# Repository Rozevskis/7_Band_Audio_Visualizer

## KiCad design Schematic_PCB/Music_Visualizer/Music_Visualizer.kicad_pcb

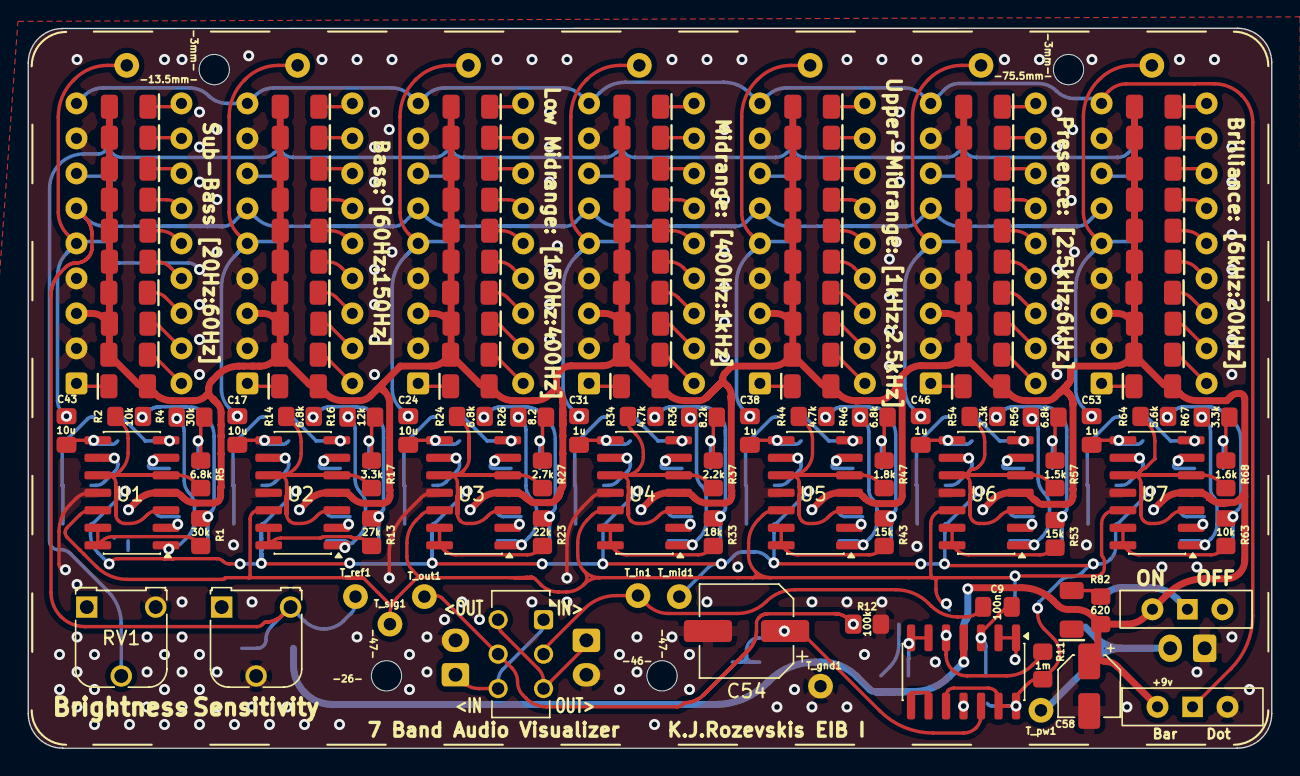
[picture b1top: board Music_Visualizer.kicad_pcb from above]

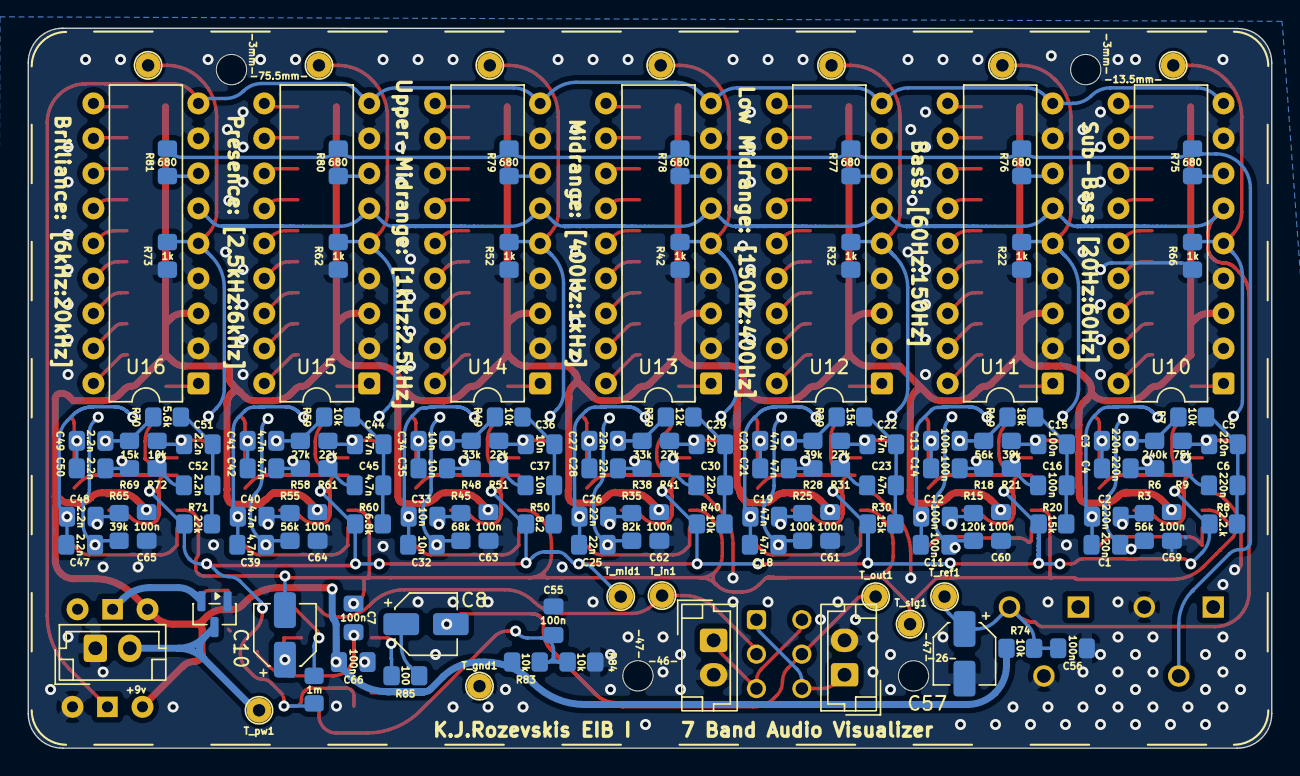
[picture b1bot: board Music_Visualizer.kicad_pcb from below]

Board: 2 copper layers, 90.2 x 52.2 mm, 264 parts (135 on the bottom side), 175 nets.

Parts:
C1, C2, C3, C4, C5, C6: 220n; custom_C_0805_2012Metric_Pad1.18x1.45mm_HandSolder
C7, C9, C11, C12, C13, C14, C15, C16, C55, C56, C59, C60, C61, C62, C63, C64, C65, C66: 100n; custom_C_0805_2012Metric_Pad1.18x1.45mm_HandSolder
C8, C10, C57, C58: 10u; CP_Elec_4x5.4
C17, C24, C43: 10u; custom_C_0805_2012Metric_Pad1.18x1.45mm_HandSolder
C18, C19, C20, C21, C22, C23: 47n; custom_C_0805_2012Metric_Pad1.18x1.45mm_HandSolder
C25, C26, C27, C28, C29, C30: 22n; custom_C_0805_2012Metric_Pad1.18x1.45mm_HandSolder
C31, C38, C46, C53: 1u; custom_C_0805_2012Metric_Pad1.18x1.45mm_HandSolder
C32, C33, C34, C35, C36, C37: 10n; custom_C_0805_2012Metric_Pad1.18x1.45mm_HandSolder
C39, C40, C41, C42, C44, C45: 4.7n; custom_C_0805_2012Metric_Pad1.18x1.45mm_HandSolder
C47, C48, C49, C50, C51, C52: 2.2n; custom_C_0805_2012Metric_Pad1.18x1.45mm_HandSolder
C54: 47u; CP_Elec_6.3x5.3
D1, D2, D3, D4, D5, D6, D7, D11, D12, D13, D14, D15, D16, D17, D21, D22, D23, D24, D25, D26, D27, D31, D32, D33, D34, D35, D36, D37, D41, D42, D43, D44, D45, D46, D47, D51, D52, D53, D54, D55, D56, D57, D61, D62, D63, D64, D65, D66, D67: LED; LED_1206_3216Metric_Green
D8, D9, D18, D19, D28, D29, D38, D39, D48, D49, D58, D59, D68, D69: LED; LED_1206_3216Metric_Yellow
D10, D20, D30, D40, D50, D60, D70, D71: LED; LED_1206_3216Metric_Red
H1, H2, H3, H4: MountingHole; Apgriezts_MountingHole_2.2mm_M2
J3, J5: Screw_Terminal_01x02; JST_EH_B2B-EH-A_1x02_P2.50mm_Vertical
J6: 3.5mm; JST_EH_B2B-EH-A_1x02_P2.50mm_Vertical
Q1: DMP2123LQ-7; SOT-23
R1, R4: 30k; R_0805_2012Metric_Pad1.20x1.40mm_HandSolder
R2, R7, R40, R49, R59, R63, R72, R74, R83, R84: 10k; R_0805_2012Metric_Pad1.20x1.40mm_HandSolder
R3, R18, R55: 56k; R_0805_2012Metric_Pad1.20x1.40mm_HandSolder
R5, R14, R24, R46, R56, R60: 6.8k; R_0805_2012Metric_Pad1.20x1.40mm_HandSolder
R6: 240k; R_0805_2012Metric_Pad1.20x1.40mm_HandSolder
R8: 2.2.k; R_0805_2012Metric_Pad1.20x1.40mm_HandSolder
R9: 75k; R_0805_2012Metric_Pad1.20x1.40mm_HandSolder
R10, R11: 1m; R_0805_2012Metric_Pad1.20x1.40mm_HandSolder
R12, R25: 100k; R_0805_2012Metric_Pad1.20x1.40mm_HandSolder
R13, R31, R41, R58: 27k; R_0805_2012Metric_Pad1.20x1.40mm_HandSolder
R15: 120k; R_0805_2012Metric_Pad1.20x1.40mm_HandSolder
R16, R39: 12k; R_0805_2012Metric_Pad1.20x1.40mm_HandSolder
R17, R54, R67: 3.3k; R_0805_2012Metric_Pad1.20x1.40mm_HandSolder
R19, R33: 18k; R_0805_2012Metric_Pad1.20x1.40mm_HandSolder
R20, R29, R30, R43, R53, R69: 15k; R_0805_2012Metric_Pad1.20x1.40mm_HandSolder
R21, R28, R65: 39k; R_0805_2012Metric_Pad1.20x1.40mm_HandSolder
R22, R32, R42, R52, R62, R66, R73: 1k; R_0805_2012Metric_Pad1.20x1.40mm_HandSolder
R23, R51, R61, R71: 22k; R_0805_2012Metric_Pad1.20x1.40mm_HandSolder
R26, R50: 8.2; R_0805_2012Metric_Pad1.20x1.40mm_HandSolder
R27: 2.7k; R_0805_2012Metric_Pad1.20x1.40mm_HandSolder
R34, R44: 4.7k; R_0805_2012Metric_Pad1.20x1.40mm_HandSolder
R35: 82k; R_0805_2012Metric_Pad1.20x1.40mm_HandSolder
R36: 8.2k; R_0805_2012Metric_Pad1.20x1.40mm_HandSolder
R37: 2.2k; R_0805_2012Metric_Pad1.20x1.40mm_HandSolder
R38, R48: 33k; R_0805_2012Metric_Pad1.20x1.40mm_HandSolder
R45: 68k; R_0805_2012Metric_Pad1.20x1.40mm_HandSolder
R47: 1.8k; R_0805_2012Metric_Pad1.20x1.40mm_HandSolder
R57: 1.5k; R_0805_2012Metric_Pad1.20x1.40mm_HandSolder
R64, R70: 5.6k; R_0805_2012Metric_Pad1.20x1.40mm_HandSolder
R68: 1.6k; R_0805_2012Metric_Pad1.20x1.40mm_HandSolder
R75, R76, R77, R78, R79, R80, R81: 680; R_0805_2012Metric_Pad1.20x1.40mm_HandSolder
R82: 620; R_0805_2012Metric_Pad1.20x1.40mm_HandSolder
R85: 100; R_0805_2012Metric_Pad1.20x1.40mm_HandSolder
RV1: 1k_LED_Brightness_Pot; Potentiometer_Runtron_RM-065_Vertical
RV2: 1k_Rhi_Adjuster; Potentiometer_Runtron_RM-065_Vertical
SW1: SW_Slide_DPDT; SW_CK_JS202011CQN_DPDT_Straight
SW2, SW3: SW_SPST; SW_Slide-03_Wuerth-WS-SLTV_10x2.5x6.4_P2.54mm
TP1: T_SB; NEW_2_TestPoint_Loop_D2.60mm_Drill0.9mm_Beaded
TP2: T_B; NEW_2_TestPoint_Loop_D2.60mm_Drill0.9mm_Beaded
TP3: T_LM; NEW_2_TestPoint_Loop_D2.60mm_Drill0.9mm_Beaded
TP4: T_M; NEW_2_TestPoint_Loop_D2.60mm_Drill0.9mm_Beaded
TP5: T_UM; NEW_2_TestPoint_Loop_D2.60mm_Drill0.9mm_Beaded
TP6: V_MH; NEW_2_TestPoint_Loop_D2.60mm_Drill0.9mm_Beaded
TP7: V_H; NEW_2_TestPoint_Loop_D2.60mm_Drill0.9mm_Beaded
T_gnd1: T_gnd; NEW_2_TestPoint_Loop_D2.60mm_Drill0.9mm_Beaded
T_in1: T_in; NEW_2_TestPoint_Loop_D2.60mm_Drill0.9mm_Beaded
T_mid1: T_mid; NEW_2_TestPoint_Loop_D2.60mm_Drill0.9mm_Beaded
T_out1: T_out; NEW_2_TestPoint_Loop_D2.60mm_Drill0.9mm_Beaded
T_pw1: T_pw; NEW_2_TestPoint_Loop_D2.60mm_Drill0.9mm_Beaded
T_ref1: T_ref; NEW_2_TestPoint_Loop_D2.60mm_Drill0.9mm_Beaded
T_sig1: T_sig; NEW_2_TestPoint_Loop_D2.60mm_Drill0.9mm_Beaded
U1, U2, U3, U4, U5, U6, U7, U8: LM324; SOIC-14_3.9x8.7mm_P1.27mm
U10, U11, U12, U13, U14, U15, U16: LM3915N-1; DIP-18_W7.62mm

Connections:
+9V: C58.1, C59.2, C60.2, C61.2, C62.2, C63.2, C64.2, C65.2, C66.2, D1.2 (A), D2.2 (A), D3.2 (A), D4.2 (A), D5.2 (A), D6.2 (A), D7.2 (A), D8.2 (A), D9.2 (A), D10.2 (A), D11.2 (A), D12.2 (A), D13.2 (A), D14.2 (A), D15.2 (A), D16.2 (A), D17.2 (A), D18.2 (A), D19.2 (A), D20.2 (A), D21.2 (A), D22.2 (A), D23.2 (A), D24.2 (A), D25.2 (A), D26.2 (A), D27.2 (A), D28.2 (A), D29.2 (A), D30.2 (A), D31.2 (A), D32.2 (A), D33.2 (A), D34.2 (A), D35.2 (A), D36.2 (A), D37.2 (A), D38.2 (A), D39.2 (A), D40.2 (A), D41.2 (A), D42.2 (A), D43.2 (A), D44.2 (A), D45.2 (A), D46.2 (A), D47.2 (A), D48.2 (A), D49.2 (A), D50.2 (A), D51.2 (A), D52.2 (A), D53.2 (A), D54.2 (A), D55.2 (A), D56.2 (A), D57.2 (A), D58.2 (A), D59.2 (A), D60.2 (A), D61.2 (A), D62.2 (A), D63.2 (A), D64.2 (A), D65.2 (A), D66.2 (A), D67.2 (A), D68.2 (A), D69.2 (A), D70.2 (A), R74.1, R82.1, R83.2, SW2.2 (B), SW3.1 (C), U1.4 (V+), U2.4 (V+), U3.4 (V+), U4.4 (V+), U5.4 (V+), U6.4 (V+), U7.4 (V+), U8.4 (V+), U10.3 (V+), U11.3 (V+), U12.3 (V+), U13.3 (V+), U14.3 (V+), U15.3 (V+), U16.3 (V+)
GND: C54.2, C55.1, C56.1, C57.2, C58.2, C59.1, C60.1, C61.1, C62.1, C63.1, C64.1, C65.1, C66.1, D71.1 (K), J3.2, J5.2, J6.1 (-), Q1.2 (G), R12.2, R22.2, R32.2, R42.2, R52.2, R62.2, R66.2, R73.2, R84.1, RV1.3, RV2.2, SW3.3 (A), T_gnd1.1 (1_1), U1.11 (V-), U2.11 (V-), U3.11 (V-), U4.11 (V-), U5.11 (V-), U6.11 (V-), U7.11 (V-), U8.11 (V-), U10.2 (V-), U10.4 (RLO), U10.8 (REF_ADJ), U11.2 (V-), U11.4 (RLO), U11.8 (REF_ADJ), U12.2 (V-), U12.4 (RLO), U12.8 (REF_ADJ), U13.2 (V-), U13.4 (RLO), U13.8 (REF_ADJ), U14.2 (V-), U14.4 (RLO), U14.8 (REF_ADJ), U15.2 (V-), U15.4 (RLO), U15.8 (REF_ADJ), U16.2 (V-), U16.4 (RLO), U16.8 (REF_ADJ)
LED_Brightness_Control: R75.2, R76.2, R77.2, R78.2, R79.2, R80.2, R81.2, RV1.2
Left jack: J3.1, SW1.1 (A), SW1.4 (A)
Mode: SW3.2 (B), U10.9 (MODE), U11.9 (MODE), U12.9 (MODE), U13.9 (MODE), U14.9 (MODE), U15.9 (MODE), U16.9 (MODE)
unnamed: C1.1, C2.1, R1.2, R2.1
unnamed: C1.2, R3.1, R4.1, U1.1
unnamed: C3.1, C4.1, R4.2, R5.1
unnamed: C3.2, R6.1, R7.1, U1.7
unnamed: C5.1, C6.1, R7.2, R8.1
unnamed: C8.1, R85.2
unnamed: C8.2, R12.1, SW1.5 (B), T_out1.1 (1_1)
unnamed: C9.1, SW1.2 (B), T_in1.1 (1_1)
unnamed: C11.1, C12.1, R13.2, R14.1
unnamed: C11.2, R15.1, R16.1, U2.1
unnamed: C13.1, C14.1, R16.2, R17.1
unnamed: C13.2, R18.1, R19.1, U2.7
unnamed: C15.1, C16.1, R19.2, R20.1
unnamed: C15.2, C17.1, R21.1, U2.8
unnamed: C18.1, C19.1, R23.2, R24.1
unnamed: C18.2, R25.1, R26.1, U3.1
unnamed: C20.1, C21.1, R26.2, R27.1
unnamed: C20.2, R28.1, R29.1, U3.7
unnamed: C22.1, C23.1, R29.2, R30.1
unnamed: C22.2, C24.1, R31.1, U3.8
unnamed: C25.1, C26.1, R33.2, R34.1
unnamed: C25.2, R35.1, R36.1, U4.1
unnamed: C27.1, C28.1, R36.2, R37.1
unnamed: C27.2, R38.1, R39.1, U4.7
unnamed: C29.1, C30.1, R39.2, R40.1
unnamed: C29.2, C31.1, R41.1, U4.8
unnamed: C32.1, C33.1, R43.2, R44.1
unnamed: C32.2, R45.1, R46.1, U5.1
unnamed: C34.1, C35.1, R46.2, R47.1
unnamed: C34.2, R48.1, R49.1, U5.7
unnamed: C36.1, C37.1, R49.2, R50.1
unnamed: C36.2, C38.1, R51.1, U5.8
unnamed: C39.1, C40.1, R53.2, R54.1
unnamed: C39.2, R55.1, R56.1, U6.1
unnamed: C41.1, C42.1, R56.2, R57.1
unnamed: C41.2, R58.1, R59.1, U6.7
unnamed: C5.2, C43.2, R9.1, U1.8
unnamed: C44.1, C45.1, R59.2, R60.1
unnamed: C44.2, C46.1, R61.1, U6.8
unnamed: C47.1, C48.1, R63.2, R64.1
unnamed: C47.2, R65.1, R67.1, U7.1
unnamed: C49.1, C50.1, R67.2, R68.1
unnamed: C49.2, R69.1, R70.1, U7.7
unnamed: C51.1, C52.1, R70.2, R71.1
unnamed: C51.2, C53.1, R72.1, U7.8
unnamed: D1.1 (K), U10.1 (LED1_K)
unnamed: D2.1 (K), U10.18 (LED2_K)
unnamed: D3.1 (K), U10.17 (LED3_K)
unnamed: D4.1 (K), U10.16 (LED4_K)
unnamed: D5.1 (K), U10.15 (LED5_K)
unnamed: D6.1 (K), U10.14 (LED6_K)
unnamed: D7.1 (K), U10.13 (LED7_K)
unnamed: D8.1 (K), U10.12 (LED8_K)
unnamed: D9.1 (K), U10.11 (LED9_K)
unnamed: D10.1 (K), U10.10 (LED10_K)
unnamed: D11.1 (K), U11.1 (LED1_K)
unnamed: D12.1 (K), U11.18 (LED2_K)
unnamed: D13.1 (K), U11.17 (LED3_K)
unnamed: D14.1 (K), U11.16 (LED4_K)
unnamed: D15.1 (K), U11.15 (LED5_K)
unnamed: D16.1 (K), U11.14 (LED6_K)
unnamed: D17.1 (K), U11.13 (LED7_K)
unnamed: D18.1 (K), U11.12 (LED8_K)
unnamed: D19.1 (K), U11.11 (LED9_K)
unnamed: D20.1 (K), U11.10 (LED10_K)
unnamed: D21.1 (K), U12.1 (LED1_K)
unnamed: D22.1 (K), U12.18 (LED2_K)
unnamed: D23.1 (K), U12.17 (LED3_K)
unnamed: D24.1 (K), U12.16 (LED4_K)
unnamed: D25.1 (K), U12.15 (LED5_K)
unnamed: D26.1 (K), U12.14 (LED6_K)
unnamed: D27.1 (K), U12.13 (LED7_K)
unnamed: D28.1 (K), U12.12 (LED8_K)
unnamed: D29.1 (K), U12.11 (LED9_K)
unnamed: D30.1 (K), U12.10 (LED10_K)
unnamed: D31.1 (K), U13.1 (LED1_K)
unnamed: D32.1 (K), U13.18 (LED2_K)
unnamed: D33.1 (K), U13.17 (LED3_K)
unnamed: D34.1 (K), U13.16 (LED4_K)
unnamed: D35.1 (K), U13.15 (LED5_K)
unnamed: D36.1 (K), U13.14 (LED6_K)
unnamed: D37.1 (K), U13.13 (LED7_K)
unnamed: D38.1 (K), U13.12 (LED8_K)
unnamed: D39.1 (K), U13.11 (LED9_K)
unnamed: D40.1 (K), U13.10 (LED10_K)
unnamed: D41.1 (K), U14.1 (LED1_K)
unnamed: D42.1 (K), U14.18 (LED2_K)
unnamed: D43.1 (K), U14.17 (LED3_K)
unnamed: D44.1 (K), U14.16 (LED4_K)
unnamed: D45.1 (K), U14.15 (LED5_K)
unnamed: D46.1 (K), U14.14 (LED6_K)
unnamed: D47.1 (K), U14.13 (LED7_K)
unnamed: D48.1 (K), U14.12 (LED8_K)
unnamed: D49.1 (K), U14.11 (LED9_K)
unnamed: D50.1 (K), U14.10 (LED10_K)
unnamed: D51.1 (K), U15.1 (LED1_K)
unnamed: D52.1 (K), U15.18 (LED2_K)
unnamed: D53.1 (K), U15.17 (LED3_K)
unnamed: D54.1 (K), U15.16 (LED4_K)
unnamed: D55.1 (K), U15.15 (LED5_K)
unnamed: D56.1 (K), U15.14 (LED6_K)
unnamed: D57.1 (K), U15.13 (LED7_K)
unnamed: D58.1 (K), U15.12 (LED8_K)
unnamed: D59.1 (K), U15.11 (LED9_K)
unnamed: D60.1 (K), U15.10 (LED10_K)
unnamed: D61.1 (K), U16.1 (LED1_K)
unnamed: D62.1 (K), U16.18 (LED2_K)
unnamed: D63.1 (K), U16.17 (LED3_K)
unnamed: D64.1 (K), U16.16 (LED4_K)
unnamed: D65.1 (K), U16.15 (LED5_K)
unnamed: D66.1 (K), U16.14 (LED6_K)
unnamed: D67.1 (K), U16.13 (LED7_K)
unnamed: D68.1 (K), U16.12 (LED8_K)
unnamed: D69.1 (K), U16.11 (LED9_K)
unnamed: D70.1 (K), U16.10 (LED10_K)
unnamed: D71.2 (A), R82.2
unnamed: J6.2 (+), Q1.1 (D), T_pw1.1 (1_1)
unnamed: Q1.3 (S), SW2.1 (A)
unnamed: C2.2, R3.2, U1.2 (-)
unnamed: C4.2, R6.2, U1.6 (-)
unnamed: C6.2, R9.2, U1.9 (-)
unnamed: R1.1, U1.13 (-), U1.14
unnamed: C12.2, R15.2, U2.2 (-)
unnamed: C14.2, R18.2, U2.6 (-)
unnamed: C16.2, R21.2, U2.9 (-)
unnamed: R13.1, U2.13 (-), U2.14
unnamed: C19.2, R25.2, U3.2 (-)
unnamed: C21.2, R28.2, U3.6 (-)
unnamed: C23.2, R31.2, U3.9 (-)
unnamed: R23.1, U3.13 (-), U3.14
unnamed: C26.2, R35.2, U4.2 (-)
unnamed: C28.2, R38.2, U4.6 (-)
unnamed: C30.2, R41.2, U4.9 (-)
unnamed: R33.1, U4.13 (-), U4.14
unnamed: C33.2, R45.2, U5.2 (-)
unnamed: C35.2, R48.2, U5.6 (-)
unnamed: C37.2, R51.2, U5.9 (-)
unnamed: R43.1, U5.13 (-), U5.14
unnamed: C40.2, R55.2, U6.2 (-)
unnamed: C42.2, R58.2, U6.6 (-)
unnamed: C45.2, R61.2, U6.9 (-)
unnamed: R53.1, U6.13 (-), U6.14
unnamed: C48.2, R65.2, U7.2 (-)
unnamed: C50.2, R69.2, U7.6 (-)
unnamed: C52.2, R72.2, U7.9 (-)
unnamed: R63.1, U7.13 (-), U7.14
unnamed: C9.2, R10.1, U8.3 (+)
unnamed: C10.1, U8.1, U8.2 (-)
unnamed: C7.2, R11.1, U8.5 (+)
unnamed: R85.1, U8.6 (-), U8.7
unnamed: U8.8, U8.9 (-)
unnamed: C54.1, C55.2, R83.1, R84.2, U8.12 (+)
unnamed: R75.1, U10.7 (REF_OUT)
unnamed: R76.1, U11.7 (REF_OUT)
unnamed: R77.1, U12.7 (REF_OUT)
unnamed: R78.1, U13.7 (REF_OUT)
unnamed: R79.1, U14.7 (REF_OUT)
unnamed: R80.1, U15.7 (REF_OUT)
unnamed: R81.1, U16.7 (REF_OUT)
Rhi_Value: C56.2, C57.1, R74.2, RV2.3, T_ref1.1 (1_1), U10.6 (RHI), U11.6 (RHI), U12.6 (RHI), U13.6 (RHI), U14.6 (RHI), U15.6 (RHI), U16.6 (RHI)
Right jack: J5.1, SW1.3 (C), SW1.6 (C)
VBass: C17.2, R22.1, TP2.1 (1_1), U11.5 (SIG)
VBrilliance: C53.2, R73.1, TP7.1 (1_1), U16.5 (SIG)
VCC4_5: R2.2, R5.2, R8.2, R10.2, R11.2, R14.2, R17.2, R20.2, R24.2, R27.2, R30.2, R34.2, R37.2, R40.2, R44.2, R47.2, R50.2, R54.2, R57.2, R60.2, R64.2, R68.2, R71.2, T_mid1.1 (1_1), U1.3 (+), U1.5 (+), U1.10 (+), U2.3 (+), U2.5 (+), U2.10 (+), U3.3 (+), U3.5 (+), U3.10 (+), U4.3 (+), U4.5 (+), U4.10 (+), U5.3 (+), U5.5 (+), U5.10 (+), U6.3 (+), U6.5 (+), U6.10 (+), U7.3 (+), U7.5 (+), U7.10 (+), U8.10 (+), U8.13 (-), U8.14
VLowerMidrange: C24.2, R32.1, TP3.1 (1_1), U12.5 (SIG)
VMidrange: C31.2, R42.1, TP4.1 (1_1), U13.5 (SIG)
VPresence: C46.2, R62.1, TP6.1 (1_1), U15.5 (SIG)
VSubBass: C43.1, R66.1, TP1.1 (1_1), U10.5 (SIG)
VUpperMidrange: C38.2, R52.1, TP5.1 (1_1), U14.5 (SIG)
Vsig: C7.1, C10.2, T_sig1.1 (1_1), U1.12 (+), U2.12 (+), U3.12 (+), U4.12 (+), U5.12 (+), U6.12 (+), U7.12 (+)

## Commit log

2026-03-10 Added missing LM3915 Dependancy
2026-03-30 RHi- Value controll replaced
2026-03-30 Add backups
2026-03-30 Filter test sub bass
2026-03-30 Git ignore update
2026-03-30 Replace +-5v with 9v
2026-03-31 Input buffer 20-60hz filter changed
2026-03-31 Change freq ranges to quasi-log
2026-03-31 Add output buffer
2026-03-31 Add filters with new values
2026-04-02 Change op amp exit cap
2026-04-02 Replace ideal resistors with aprox
2026-04-02 Add testpoints
2026-04-02 Gitignore update
2026-04-02 In-Out switch
2026-04-02 Correct op amps
2026-04-02 PCB LEDs placed
2026-04-02 Battery low
2026-04-02 PCB V1 done
2026-04-07 Chnge diode footprint to 1206
2026-04-08 Replace elec. cap.
2026-04-14 Fix jack reverse
2026-04-14 Change jack footprint
2026-04-16 Change Barrel jack footprint
2026-04-16 Update capacitor footprint
2026-04-16 Update op amp decoupling
2026-04-16 Test layout
2026-04-17 Remove jacks and compact placement
2026-04-21 Refine traces layout
2026-04-21 pre RDC
2026-04-22 Fixed DRC erros
2026-04-22 Fixed DRC erros after round tracks
2026-04-22 Fixes and placed test points on back
2026-04-27 backup
2026-05-16 Replace filters with Chebyshev
